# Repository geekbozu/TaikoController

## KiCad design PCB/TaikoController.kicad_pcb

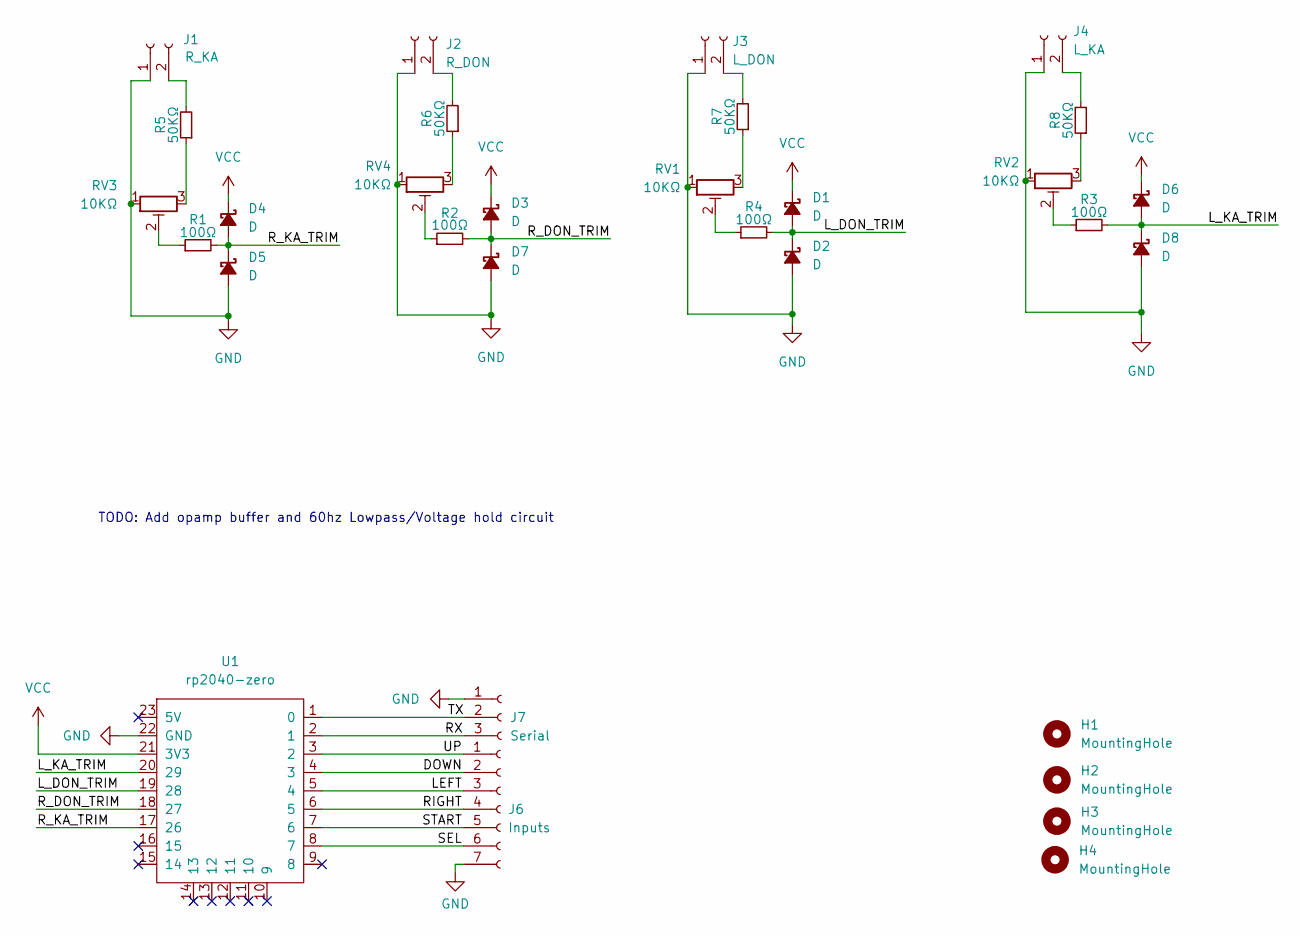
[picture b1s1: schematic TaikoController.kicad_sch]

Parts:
D1, D2, D3, D4, D5, D6, D7, D8: D; D_SOD-323_HandSoldering
H1, H2, H3, H4: MountingHole; MountingHole_2.2mm_M2
J1: R_KA; PinHeader_1x02_P2.54mm_Vertical
J2: R_DON; PinHeader_1x02_P2.54mm_Vertical
J3: L_DON; PinHeader_1x02_P2.54mm_Vertical
J4: L_KA; PinHeader_1x02_P2.54mm_Vertical
J6: Inputs; PinSocket_1x07_P2.54mm_Vertical
J7: Serial; PinHeader_1x03_P2.54mm_Vertical
R1, R2, R3, R4: 100Ω; R_0603_1608Metric
R5, R6, R7, R8: 50KΩ; R_0603_1608Metric
RV1, RV2, RV3, RV4: 10KΩ; BOURNS-3362P_pot
U1: rp2040-zero; rp2040-zero-tht-pads

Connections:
/DOWN: J6.2, U1.4 (3)
/LEFT: J6.3, U1.5 (4)
/L_DON_TRIM: D1.2 (A), D2.1 (K), R4.2, U1.19 (28)
/L_KA_TRIM: D6.2 (A), D8.1 (K), R3.2, U1.20 (29)
/RIGHT: J6.4, U1.6 (5)
/RX: J7.3, U1.2 (1)
/R_DON_TRIM: D3.2 (A), D7.1 (K), R2.2, U1.18 (27)
/R_KA_TRIM: D4.2 (A), D5.1 (K), R1.2, U1.17 (26)
/SEL: J6.6, U1.8 (7)
/START: J6.5, U1.7 (6)
/TX: J7.2, U1.1 (0)
/UP: J6.1, U1.3 (2)
GND: D2.2 (A), D5.2 (A), D7.2 (A), D8.2 (A), J1.1, J2.1, J3.1, J4.1, J6.7, J7.1, RV1.1, RV2.1, RV3.1, RV4.1, U1.22 (GND)
unnamed: J1.2, R5.2
unnamed: J2.2, R6.2
unnamed: J3.2, R7.2
unnamed: J4.2, R8.2
unnamed: R1.1, RV3.2
unnamed: R2.1, RV4.2
unnamed: R3.1, RV2.2
unnamed: R4.1, RV1.2
unnamed: R5.1, RV3.3
unnamed: R6.1, RV4.3
unnamed: R7.1, RV1.3
unnamed: R8.1, RV2.3
VCC: D1.1 (K), D3.1 (K), D4.1 (K), D6.1 (K), U1.21 (3V3)

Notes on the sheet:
TODO: Add opamp buffer and 60hz Lowpass/Voltage hold circuit

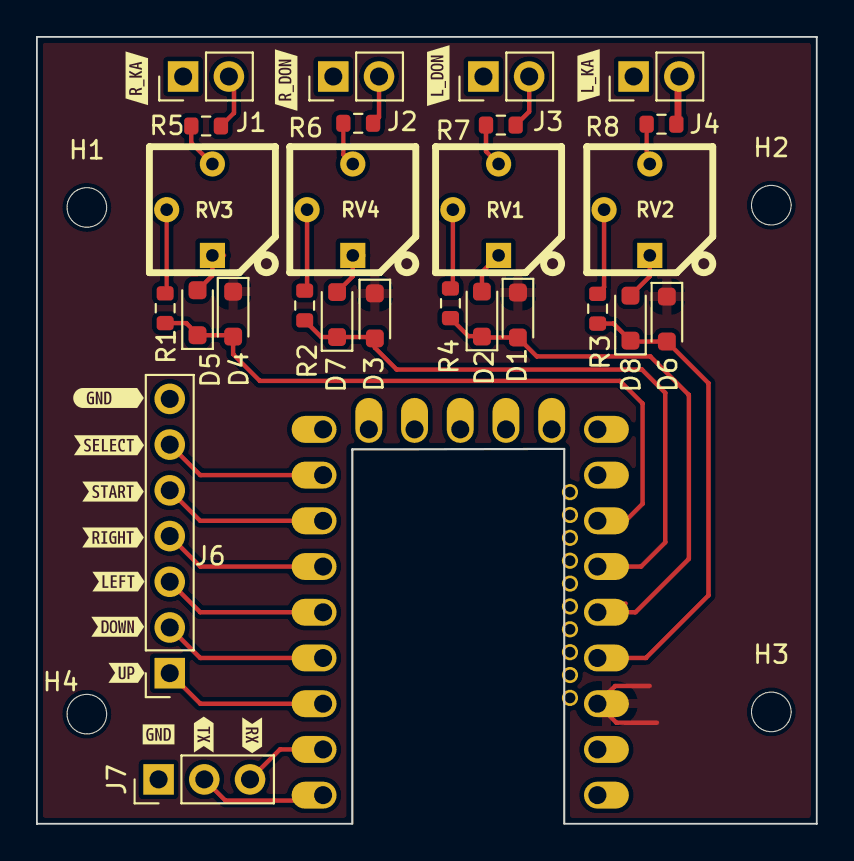
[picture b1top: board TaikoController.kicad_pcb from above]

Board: 2 copper layers, 43.3 x 43.7 mm, 45 parts (0 on the bottom side), 26 nets.

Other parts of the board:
kibuzzard-65C82ABC: G***; kibuzzard-65C82ABC
kibuzzard-65C82AC3: G***; kibuzzard-65C82AC3
kibuzzard-65C82ACA: G***; kibuzzard-65C82ACA
kibuzzard-65C82AD2: G***; kibuzzard-65C82AD2
kibuzzard-65C82AE9: G***; kibuzzard-65C82AE9
kibuzzard-65C82AFE: G***; kibuzzard-65C82AFE
kibuzzard-65C82B1C: G***; kibuzzard-65C82B1C
kibuzzard-65C82B09: G***; kibuzzard-65C82B09
kibuzzard-65C82C8B: G***; kibuzzard-65C82C8B
kibuzzard-65C82C9A: G***; kibuzzard-65C82C9A
kibuzzard-65C82C92: G***; kibuzzard-65C82C92
kibuzzard-65C82CA0: G***; kibuzzard-65C82CA0
kibuzzard-65C8290C: G***; kibuzzard-65C8290C
kibuzzard-65C82927: G***; kibuzzard-65C82927

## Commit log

2024-03-10 It actually samples the hits correct. Still needs a lot of wireup like usb
2024-03-10 Add attribution
2024-06-09 Way to much included, need to pull out attributions
2024-06-24 Initial
2024-06-25 Added mounting holes!
2024-06-26 More updates
2024-06-27 More adjustments.
